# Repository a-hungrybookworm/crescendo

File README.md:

# Crescendo

The crescendo is a custom MIDI keyboard capable of producing music from several different instruments and recording it as a MIDI file.

# Features
- Music from different instruments
- Can record music (MIDI) to be edited on a DAW
- 7 keys for 7 natural notes
- Capacitive touch keys
- Transpose functions
- Metronome and tempo additions
- Volume adjustment
- Compact PCB design

# Why it was built
The Crescendo was built for the Hack Club YSWS Programme [Halflife](https://halflife.hackclub.com/), drawing inspiration from the project [MIDI-Keypad](https://github.com/KaiPereira/MIDI-Keypad/tree/master). 

# Components
This project was built using the following components:
* WaveESP32-S3 Mini Development Board
* EC11 Rotary Encoder Modules
* Kailh switches & DSA Keycaps
* A custom PCB!

# Building it!
Drawing inspiration from the [MIDI-Keypad](https://github.com/KaiPereira/MIDI-Keypad/tree/master), I decided to make a minimal, budget-friendly version of this project - featuring 7 capacitive touch keys for each of the natural notes, volume, transpose, metronome & tempo, sounds of different instruments, and a recording feature. I have been playing the piano for six years now, so even if I don't know enough about PCB design, I do know a bit about music. 

Initially, I searched up part prices and decided which ones I could use - I had to cut down on costs as I had a costly microcontroller.

Then I figured out how to install all the footprint libraries, and connected the components on a KiCAD schematic. Initially, I didn't understand how the capacitive touch keys worked, so I added actual touch sensors to my BOM and my schematic - I was so happy when I could remove them! (- $3)

^ My initial schematic with 7 touch sensors

I used all the pins on my esp32-s3, and my final schematic looks like this-

After assigning footprints, I updated the PCB from the schematic and began to make a footprint for my rectangular capacitive touch keys. I've decided to make them 1.36 x 4cm - big enough to play them, but small enough that the PCB size remains under 100 x 100mm. I made the traces as direct as possible, and routed them. I used the front copper layer for all the traces except the ground ones, as  I found that I had enough space for all of them. 

I then added doodles to the front and the back, and finally, I added the 3D models from the MIDI repo and the Week 1 Starbie care package - finishing my PCB design!

# What I learnt 
This was one of the first hardware projects I've done, and the first music-related project I've done. I learnt a lot, including how to - 
- add footprint & symbol libraries in KiCAD, and add 3D models
- connect rotary encoders in the schematic
- add capacitive touch keys in KiCAD, with the Waveshare ESP32-S3
- add images to PCB silkscreens
- work with MIDI keyboards
- ensure PCBs remain under 100x100mm >_<

# BOM 

| Item | Qty | Supplier | Cost/item | Total Cost | Link |
|------|-----|----------|-----------|------------|------|
| WaveESP32-S3 Mini Development Board | 1 | Waveshare | $5.49 | $5.49 | [ESP32-S3](https://www.waveshare.com/esp32-s3-zero.htm?sku=25081) |
| EC11 Rotary Encoder Module | 2 | Robocraze | $0.74 | $1.48 | [EC11](https://robocraze.com/products/ec11-15mm-rotary-encoder-module?_pos=1&_sid=6ba8a4a86&_ss=r) |
| Kailh Switches (pack of 10) | 1 | Meckeys | $1.45 | $1.45 | [Kailh Switches](https://meckeys.com/shop/accessories/keyboard-accessories/key-switches/kailh-switch-pack/) |
| Blank DSA Keycaps (Set of 5) | 1 | Meckeys | $1.03 | $1.03 | [DSA Keycaps](https://meckeys.com/shop/accessories/keyboard-accessories/keycaps/blank/blank-dsa-keycaps-1u/) |
| PCB | 1 | Robu | $9.59 | $9.59 | [PCB](https://robu.in/product/online-pcb-manufacturing-service/) |
| **Parts subtotal** | | | | **$19.04** | |
| **Estimated total shipping** | | | | **$14.04** | |
| **Grand Total** | | | | **$33.08** | |

# Images and Renders 

The final schematic - 

The Crescendo PCB - 

And its backside -

^ The front (3D viewer)

^ And the back

# Credits
This project would not have been possible without the constant support of the Halflife community, and the detailed guidance given in the MIDI-Keypad guide. I loved designing this project and can't wait to build the PCB!

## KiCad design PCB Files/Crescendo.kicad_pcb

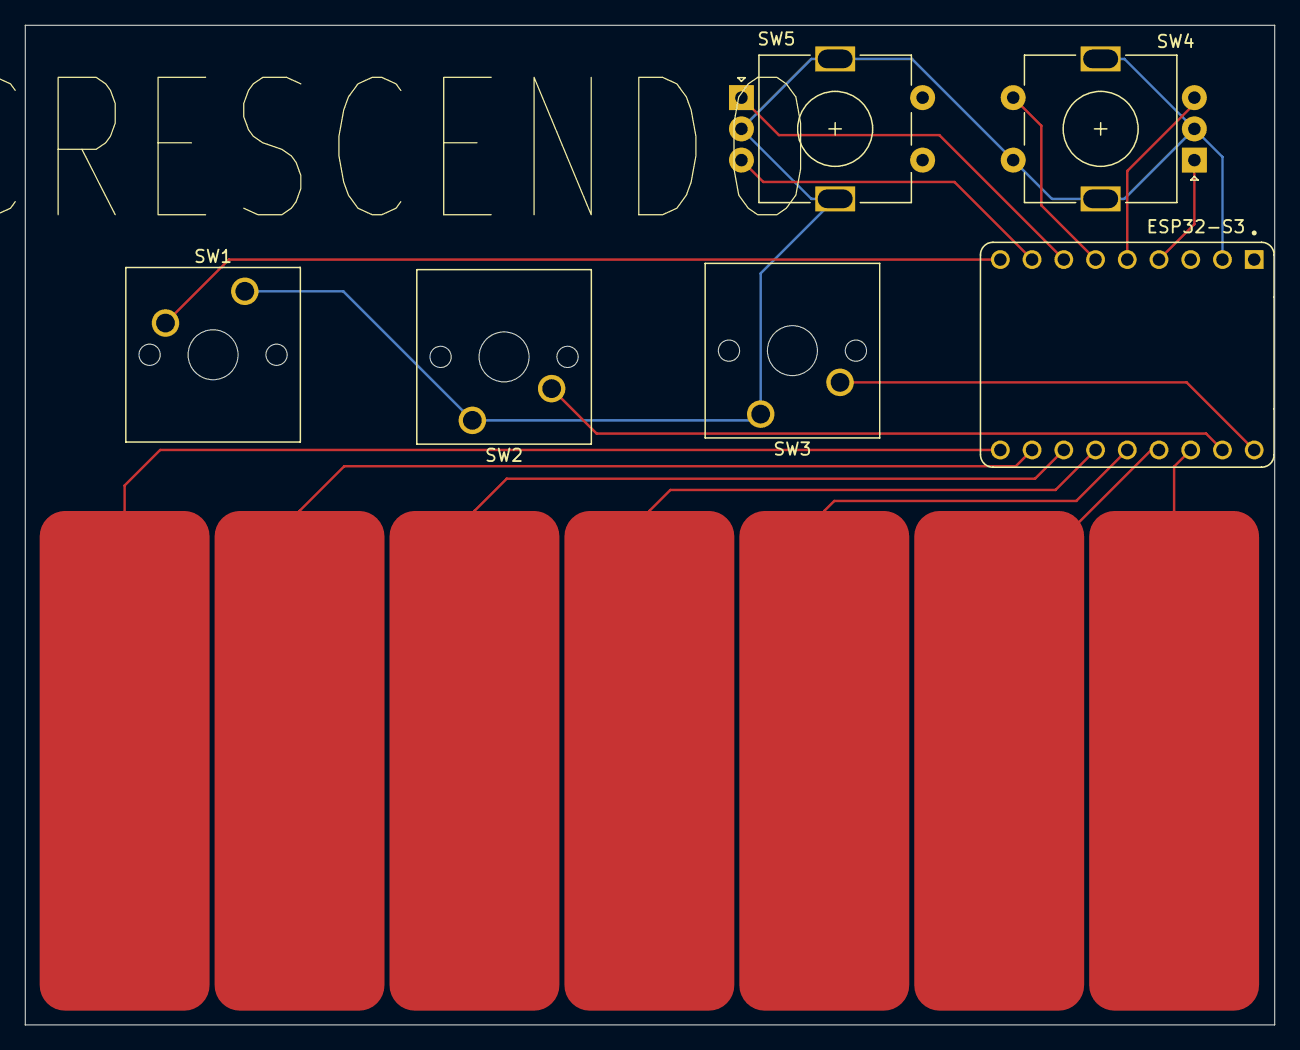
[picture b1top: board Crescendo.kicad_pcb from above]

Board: 2 copper layers, 100.0 x 80.0 mm, 7 parts (0 on the bottom side), 16 nets.

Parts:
ESP32-S3: Waveshare ESP32-S3-ZERO; Waveshare ESP32-S3-Zero
J1: Conn_01x07; 7_Keys
SW1, SW2, SW3: SW_Push; SW_Cherry_MX_1.00u_PCB
SW4, SW5: RotaryEncoder_Switch_MP; RotaryEncoder_Alps_EC11E-Switch_Vertical_H20mm

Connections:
/ENC1_A: ESP32-S3.1 (GP1), SW4.A
/ENC1_B: ESP32-S3.2 (GP2), SW4.B
/ENC2_A: ESP32-S3.4 (GP4), SW5.A
/ENC2_B: ESP32-S3.5 (GP5), SW5.B
/KEY1: ESP32-S3.7 (GP7), J1.1
/KEY2: ESP32-S3.8 (GP8), J1.2
/KEY3: ESP32-S3.9 (GP9), J1.3
/KEY4: ESP32-S3.10 (GP10), J1.4
/KEY5: ESP32-S3.11 (GP11), J1.5
/KEY6: ESP32-S3.12 (GP12), J1.6
/KEY7: ESP32-S3.13 (GP13), J1.7
/SW1: ESP32-S3.6 (GP6), SW1.2
/SW2: ESP32-S3.RX, SW2.2
/SW3: ESP32-S3.TX, SW3.2
/SW_ENC1: ESP32-S3.3 (GP3), SW4.S1
GND: ESP32-S3.GND, SW1.1, SW2.1, SW3.1, SW4.C, SW4.MP, SW4.S2, SW5.C, SW5.MP
